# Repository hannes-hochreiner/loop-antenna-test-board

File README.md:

# Test Board for a Loop Antenna (WIP)
Breadboard compatible test board for a loop antenna using an RFM69W module.

## Trace width

There are quite a few on-line impedance calculators for PCB traces.
I chose [one](http://www.eeweb.com/toolbox/microstrip-impedance) at random.
I also compared the results with the trace calculator built into KiCad.
The required figures I looked up on the [OSH Park site](http://docs.oshpark.com/services/) and [Wikipedia](https://en.wikipedia.org/wiki/FR-4).

  * Trace thickness = 1 oz/ft² (1.37 mil)
  * Substrate hight = 63 mil
  * Trace width = 3 mm
  * Substrate dielectric = 4.35
  * Impedance = 50.4 Ohm

A trace width of 3 mm did not seem feasible to me.
However, as it turns out, reducing the substrate hight also reduces the required trace width.
Luckily, OSH Park also offers a [2 oz service with thinner boards](http://docs.oshpark.com/services/two-layer-hhdc/).

  * Trace thickness = 2.8 mil
  * Substrate hight = 30 mil
  * Trace width = 1.4 mm
  * Substrate dielectric = 4.35
  * Impedance = 50.1 Ohm

## Antenna design

I implemented the design equations given in J. Van Niekerk paper in JavaScript.
This helped guide my decisions on the PCB layout.
I decided to cut the corners to avoid 90 degree bends.

## BOM

  * 2 x 1 pF  capacitors (e.g. AVX 08052U1R0BAT2A C0G ESR ~0.1 Ohm at 500 MHz; Farnell: 7568398)
  * 1 x 82 pF capacitor (e.g. AVX 12065A820JAT2A C0G; Farnell: 2332877)
  * 1 x 6-30 pF capacitor (e.g. Murata TZC3P300A110B00 N1200ppm/°C; Farnell: 9528660)
  * 2 x 7 pin header (e.g. WR-PHD Series; Farnell: 2356159)

## References
  * [J. Van Niekerk, et al "Loop Antenna Basics and Regulatory Compliance for Short-Range Radio," microchip.com retrieved 2016-05-06]( http://ww1.microchip.com/downloads/en/DeviceDoc/RFA1%20parts%205%206%20b.pdf)

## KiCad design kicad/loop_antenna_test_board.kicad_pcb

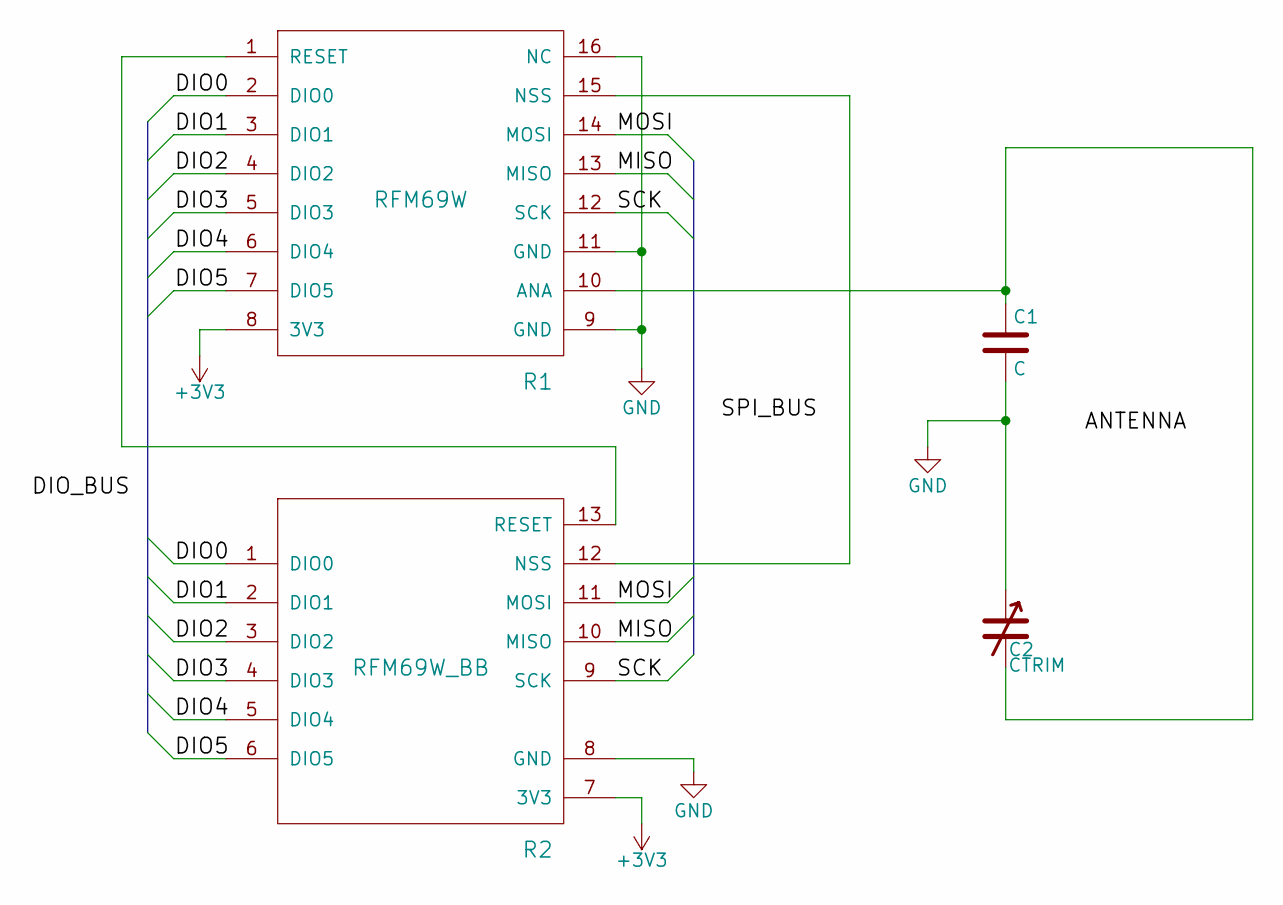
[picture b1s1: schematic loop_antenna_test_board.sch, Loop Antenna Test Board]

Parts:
C1: C; CAP
C2: CTRIM; CAP_TUNABLE
R1: RFM69W
R2: RFM69W_BB

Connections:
+3V3: R1.8 (3V3), R2.7 (3V3)
/DIO0: R1.2 (DIO0), R2.1 (DIO0)
/DIO1: R1.3 (DIO1), R2.2 (DIO1)
/DIO2: R1.4 (DIO2), R2.3 (DIO2)
/DIO3: R1.5 (DIO3), R2.4 (DIO3)
/DIO4: R1.6 (DIO4), R2.5 (DIO4)
/DIO5: R1.7 (DIO5), R2.6 (DIO5)
/MISO: R1.13 (MISO), R2.10 (MISO)
/MOSI: R1.14 (MOSI), R2.11 (MOSI)
/SCK: R1.12 (SCK), R2.9 (SCK)
GND: C1.2, C2.1, R1.9 (GND), R1.11 (GND), R1.16 (NC), R2.8 (GND)
unnamed: C1.1, C2.2, R1.10 (ANA)
unnamed: R1.1 (RESET), R2.13 (RESET)
unnamed: R1.15 (NSS), R2.12 (NSS)

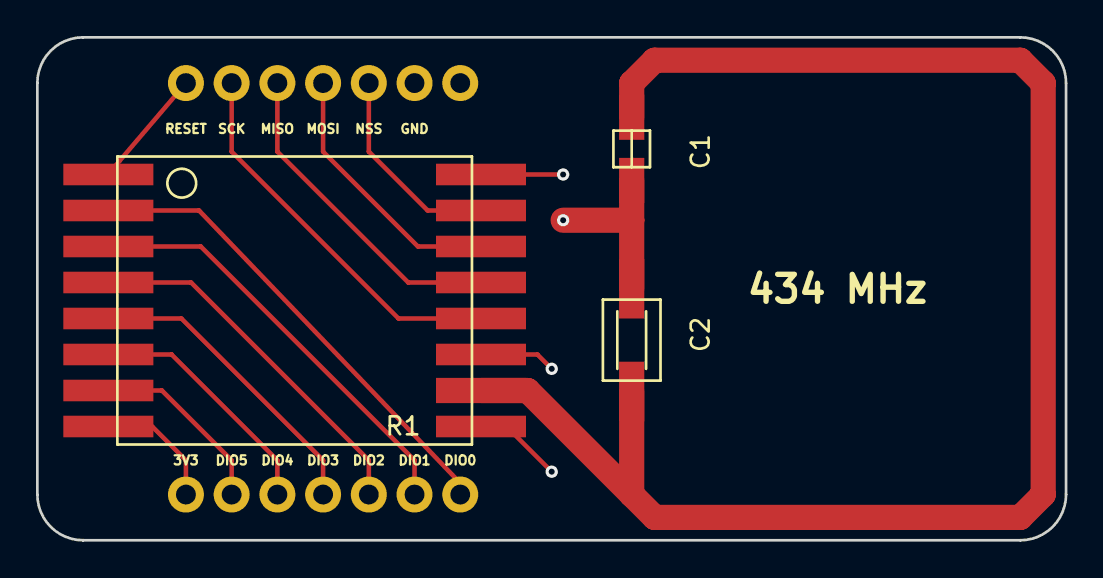
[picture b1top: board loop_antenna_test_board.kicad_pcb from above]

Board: 2 copper layers, 57.2 x 27.9 mm, 4 parts (1 on the bottom side), 14 nets.

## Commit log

2016-05-06 added utility functions for the antenna design
2016-05-08 started designing the board
2016-05-08 added board layout
2016-05-08 changed pcb layout
2016-05-08 rerouted pbc and generated gerbers
2016-05-08 updated project
2016-05-08 smoothed antenna feed
2016-05-24 added BOM
2016-05-25 switched to only having two positions for capacitors in the antenna
2016-05-25 reduced the size of the board to match it to the components
2016-05-26 added a script to help with the design of the antenna
2016-05-26 added outlines for capacitors
2016-05-26 created gerber files
2016-05-26 fixed bottom silk screen
2016-06-12 added header to BOM
2017-01-19 added secondary loop length calculation
